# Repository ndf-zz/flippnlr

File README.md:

# Flippnlr - 4x5 DiY Flipdot Panel

How _not_ to make a DiY electromechanical "Flip-Dot" matrix display.

## Coil Winding

M3 steel screw and heat shrink tube.

Shrink onto screw.

Add slight glue fillet.

Mount in winder.

Wind about 1000 turns.

Finish with a thin layer of glue.

## Flipdot Mechanism

FreeCAD model: [flipdot.FCStd](flipdot.FCStd)

SLS printed housing.

File contact areas.

Smooth contact areas with fine sandpaper.

Tap mounting and coil holes with M3 thread.

## Pixel Preparation

## Panel Assembly

Kicad PCB: [flippnlr.pro](flippnlr.pro)

## Interface

 - D Data input (SDI)
 - DC Data clock (SCK)
 - RC Latch Clock 

## License

CC0 Public Domain

To the extent possible under law, the author(s) have dedicated
all copyright and related and neighboring rights to this software
to the public domain worldwide. This software is distributed
without any warranty.

You should have received a copy of the CC0 Public Domain Dedication
along with this software. If not, see:

http://creativecommons.org/publicdomain/zero/1.0/

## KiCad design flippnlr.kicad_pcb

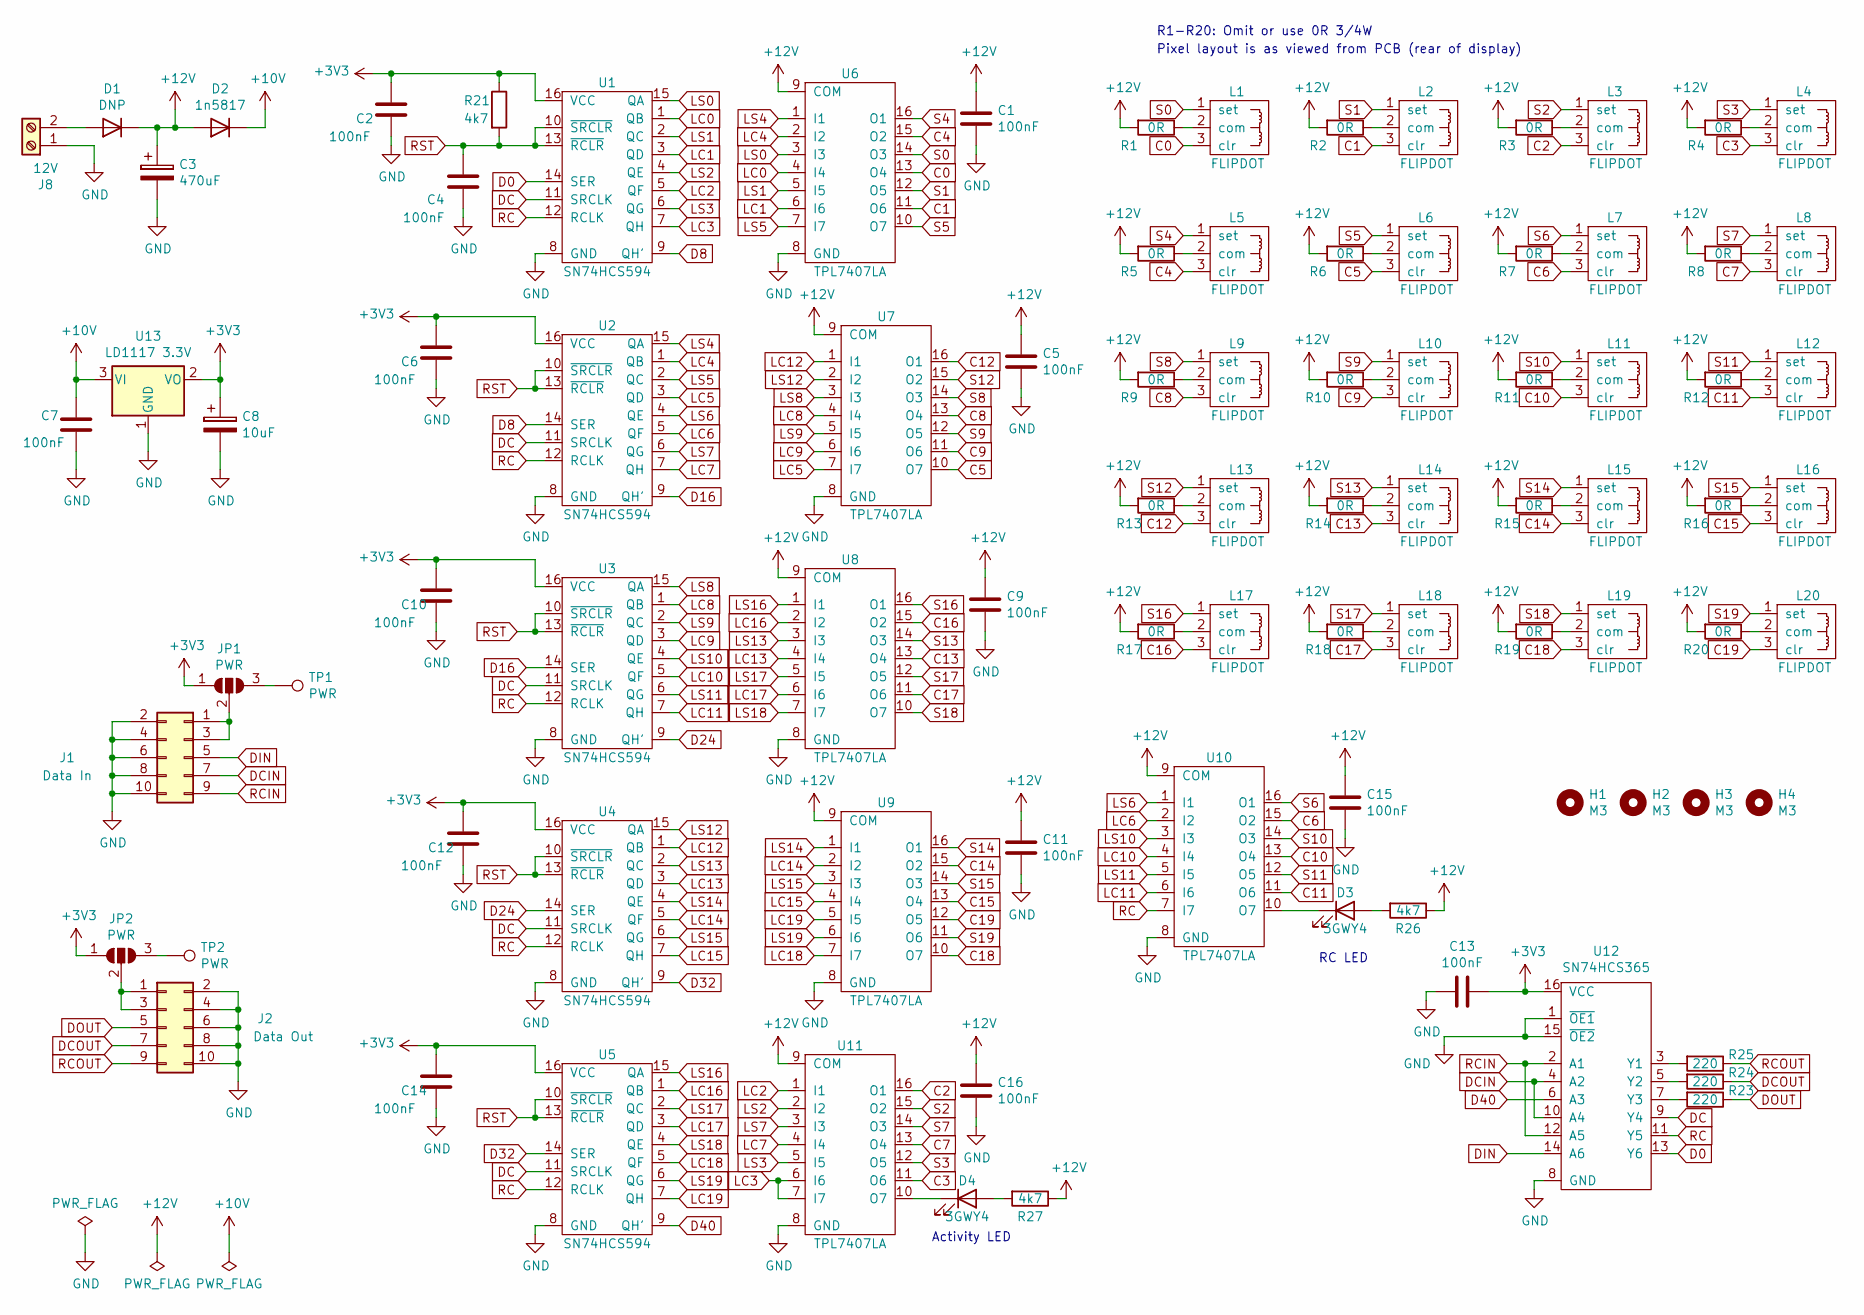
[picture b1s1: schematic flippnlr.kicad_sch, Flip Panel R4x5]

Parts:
C1, C2, C4, C5, C6, C7, C9, C10, C11, C12, C13, C14, C15, C16: 100nF; C_0805_2012Metric_Pad1.15x1.40mm_HandSolder
C3: 470uF; CP_Radial_D10.0mm_P5.00mm
C8: 10uF; CP_Radial_D5.0mm_P2.50mm
D1: DNP; D_A-405_P10.16mm_Horizontal
D2: 1n5817; D_A-405_P10.16mm_Horizontal
D3, D4: 3GWY4; LED_D3.0mm
H1, H2, H3, H4: M3; MountingHole_3.2mm_M3
J1: Data In; IDC-Header_2x05_P2.54mm_Vertical
J2: Data Out; IDC-Header_2x05_P2.54mm_Vertical
J8: 12V; TerminalBlock_Phoenix_PT-1,5-2-5.0-H_1x02_P5.00mm_Horizontal
JP1, JP2: PWR; SolderJumper-3_P1.3mm_Open_RoundedPad1.0x1.5mm
L1, L2, L3, L4, L5, L6, L7, L8, L9, L10, L11, L12, L13, L14, L15, L16, L17, L18, L19, L20: FLIPDOT; Flipdot
R1, R2, R3, R4, R5, R6, R7, R8, R9, R10, R11, R12, R13, R14, R15, R16, R17, R18, R19, R20: 0R; R_2010_5025Metric_Pad1.52x2.65mm_HandSolder
R21, R26, R27: 4k7; R_0805_2012Metric_Pad1.15x1.40mm_HandSolder
R23, R24, R25: 220; R_0805_2012Metric_Pad1.15x1.40mm_HandSolder
TP1, TP2: PWR; TestPoint_Pad_D2.0mm
U1, U2, U3, U4, U5: SN74HCS594; SOP-16_4.4x10.4mm_P1.27mm
U6, U7, U8, U9, U10, U11: TPL7407LA; SOP-16_4.4x10.4mm_P1.27mm
U12: SN74HCS365; SOP-16_4.4x10.4mm_P1.27mm
U13: LD1117 3.3V; SOT-223-3_TabPin2

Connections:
+3V3: C2.1, C6.1, C8.1, C10.1, C12.1, C13.1, C14.1, JP1.1 (A), JP2.1 (A), R21.1, U1.16 (VCC), U2.16 (VCC), U3.16 (VCC), U4.16 (VCC), U5.16 (VCC), U12.16 (VCC), U13.2 (VO)
+10V: C7.1, D2.1 (K), U13.3 (VI)
+12V: C1.1, C3.1, C5.1, C9.1, C11.1, C15.1, C16.1, D1.1 (K), D2.2 (A), R1.2, R2.2, R3.2, R4.2, R5.2, R6.2, R7.2, R8.2, R9.2, R10.2, R11.2, R12.2, R13.2, R14.2, R15.2, R16.2, R17.2, R18.2, R19.2, R20.2, R26.1, R27.1, U6.9 (COM), U7.9 (COM), U8.9 (COM), U9.9 (COM), U10.9 (COM), U11.9 (COM)
C0: L1.3 (clr), U6.13 (O4)
C1: L2.3 (clr), U6.11 (O6)
C2: L3.3 (clr), U11.16 (O1)
C3: L4.3 (clr), U11.11 (O6)
C4: L5.3 (clr), U6.15 (O2)
C5: L6.3 (clr), U7.10 (O7)
C6: L7.3 (clr), U10.15 (O2)
C7: L8.3 (clr), U11.13 (O4)
C8: L9.3 (clr), U7.13 (O4)
C9: L10.3 (clr), U7.11 (O6)
C10: L11.3 (clr), U10.13 (O4)
C11: L12.3 (clr), U10.11 (O6)
C12: L13.3 (clr), U7.16 (O1)
C13: L14.3 (clr), U8.13 (O4)
C14: L15.3 (clr), U9.15 (O2)
C15: L16.3 (clr), U9.13 (O4)
C16: L17.3 (clr), U8.15 (O2)
C17: L18.3 (clr), U8.11 (O6)
C18: L19.3 (clr), U9.10 (O7)
C19: L20.3 (clr), U9.12 (O5)
D0: U1.14 (SER), U12.13 (Y6)
D8: U1.9 (QH'), U2.14 (SER)
D16: U2.9 (QH'), U3.14 (SER)
D24: U3.9 (QH'), U4.14 (SER)
D32: U4.9 (QH'), U5.14 (SER)
D40: U5.9 (QH'), U12.6 (A3)
DC: U1.11 (SRCLK), U2.11 (SRCLK), U3.11 (SRCLK), U4.11 (SRCLK), U5.11 (SRCLK), U12.9 (Y4)
DCIN: J1.7, U12.4 (A2), U12.10 (A4)
DCOUT: J2.7, R24.1
DIN: J1.5, U12.14 (A6)
DOUT: J2.5, R23.1
GND: C1.2, C2.2, C3.2, C4.1, C5.2, C6.2, C7.2, C8.2, C9.2, C10.2, C11.2, C12.2, C13.2, C14.2, C15.2, C16.2, J1.2, J1.4, J1.6, J1.8, J1.10, J2.2, J2.4, J2.6, J2.8, J2.10, J8.1, U1.8 (GND), U2.8 (GND), U3.8 (GND), U4.8 (GND), U5.8 (GND), U6.8 (GND), U7.8 (GND), U8.8 (GND), U9.8 (GND), U10.8 (GND), U11.8 (GND), U12.1 (~OE1), U12.8 (GND), U12.15 (~OE2), U13.1 (GND)
LC0: U1.1 (QB), U6.4 (I4)
LC1: U1.3 (QD), U6.6 (I6)
LC2: U1.5 (QF), U11.1 (I1)
LC3: U1.7 (QH), U11.6 (I6), U11.7 (I7)
LC4: U2.1 (QB), U6.2 (I2)
LC5: U2.3 (QD), U7.7 (I7)
LC6: U2.5 (QF), U10.2 (I2)
LC7: U2.7 (QH), U11.4 (I4)
LC8: U3.1 (QB), U7.4 (I4)
LC9: U3.3 (QD), U7.6 (I6)
LC10: U3.5 (QF), U10.4 (I4)
LC11: U3.7 (QH), U10.6 (I6)
LC12: U4.1 (QB), U7.1 (I1)
LC13: U4.3 (QD), U8.4 (I4)
LC14: U4.5 (QF), U9.2 (I2)
LC15: U4.7 (QH), U9.4 (I4)
LC16: U5.1 (QB), U8.2 (I2)
LC17: U5.3 (QD), U8.6 (I6)
LC18: U5.5 (QF), U9.7 (I7)
LC19: U5.7 (QH), U9.5 (I5)
LS0: U1.15 (QA), U6.3 (I3)
LS1: U1.2 (QC), U6.5 (I5)
LS2: U1.4 (QE), U11.2 (I2)
LS3: U1.6 (QG), U11.5 (I5)
LS4: U2.15 (QA), U6.1 (I1)
LS5: U2.2 (QC), U6.7 (I7)
LS6: U2.4 (QE), U10.1 (I1)
LS7: U2.6 (QG), U11.3 (I3)
LS8: U3.15 (QA), U7.3 (I3)
LS9: U3.2 (QC), U7.5 (I5)
LS10: U3.4 (QE), U10.3 (I3)
LS11: U3.6 (QG), U10.5 (I5)
LS12: U4.15 (QA), U7.2 (I2)
LS13: U4.2 (QC), U8.3 (I3)
LS14: U4.4 (QE), U9.1 (I1)
LS15: U4.6 (QG), U9.3 (I3)
LS16: U5.15 (QA), U8.1 (I1)
LS17: U5.2 (QC), U8.5 (I5)
LS18: U5.4 (QE), U8.7 (I7)
LS19: U5.6 (QG), U9.6 (I6)
unnamed: D1.2 (A), J8.2
unnamed: D3.1 (K), U10.10 (O7)
unnamed: D3.2 (A), R26.2
unnamed: D4.1 (K), U11.10 (O7)
unnamed: D4.2 (A), R27.2
unnamed: J1.1, J1.3, JP1.2 (C)
unnamed: J2.1, J2.3, JP2.2 (C)
unnamed: JP1.3 (B), TP1.1
unnamed: JP2.3 (B), TP2.1
unnamed: L1.2 (com), R1.1
unnamed: L2.2 (com), R2.1
unnamed: L3.2 (com), R3.1
unnamed: L4.2 (com), R4.1
unnamed: L5.2 (com), R5.1
unnamed: L6.2 (com), R6.1
unnamed: L7.2 (com), R7.1
unnamed: L8.2 (com), R8.1
unnamed: L9.2 (com), R9.1
unnamed: L10.2 (com), R10.1
unnamed: L11.2 (com), R11.1
unnamed: L12.2 (com), R12.1
unnamed: L13.2 (com), R13.1
unnamed: L14.2 (com), R14.1
unnamed: L15.2 (com), R15.1
unnamed: L16.2 (com), R16.1
unnamed: L17.2 (com), R17.1
unnamed: L18.2 (com), R18.1
unnamed: L19.2 (com), R19.1
unnamed: L20.2 (com), R20.1
unnamed: R23.2, U12.7 (Y3)
unnamed: R24.2, U12.5 (Y2)
unnamed: R25.2, U12.3 (Y1)
RC: U1.12 (RCLK), U2.12 (RCLK), U3.12 (RCLK), U4.12 (RCLK), U5.12 (RCLK), U10.7 (I7), U12.11 (Y5)
RCIN: J1.9, U12.2 (A1), U12.12 (A5)
RCOUT: J2.9, R25.1
RST: C4.2, R21.2, U1.10 (~SRCLR), U1.13 (~RCLR), U2.10 (~SRCLR), U2.13 (~RCLR), U3.10 (~SRCLR), U3.13 (~RCLR), U4.10 (~SRCLR), U4.13 (~RCLR), U5.10 (~SRCLR), U5.13 (~RCLR)
S0: L1.1 (set), U6.14 (O3)
S1: L2.1 (set), U6.12 (O5)
S2: L3.1 (set), U11.15 (O2)
S3: L4.1 (set), U11.12 (O5)
S4: L5.1 (set), U6.16 (O1)
S5: L6.1 (set), U6.10 (O7)
S6: L7.1 (set), U10.16 (O1)
S7: L8.1 (set), U11.14 (O3)
S8: L9.1 (set), U7.14 (O3)
S9: L10.1 (set), U7.12 (O5)
S10: L11.1 (set), U10.14 (O3)
S11: L12.1 (set), U10.12 (O5)
S12: L13.1 (set), U7.15 (O2)
S13: L14.1 (set), U8.14 (O3)
S14: L15.1 (set), U9.16 (O1)
S15: L16.1 (set), U9.14 (O3)
S16: L17.1 (set), U8.16 (O1)
S17: L18.1 (set), U8.12 (O5)
S18: L19.1 (set), U8.10 (O7)
S19: L20.1 (set), U9.11 (O6)

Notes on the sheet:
R1-R20: Omit or use 0R 3/4W
RC LED
Pixel layout is as viewed from PCB (rear of display)
Activity LED

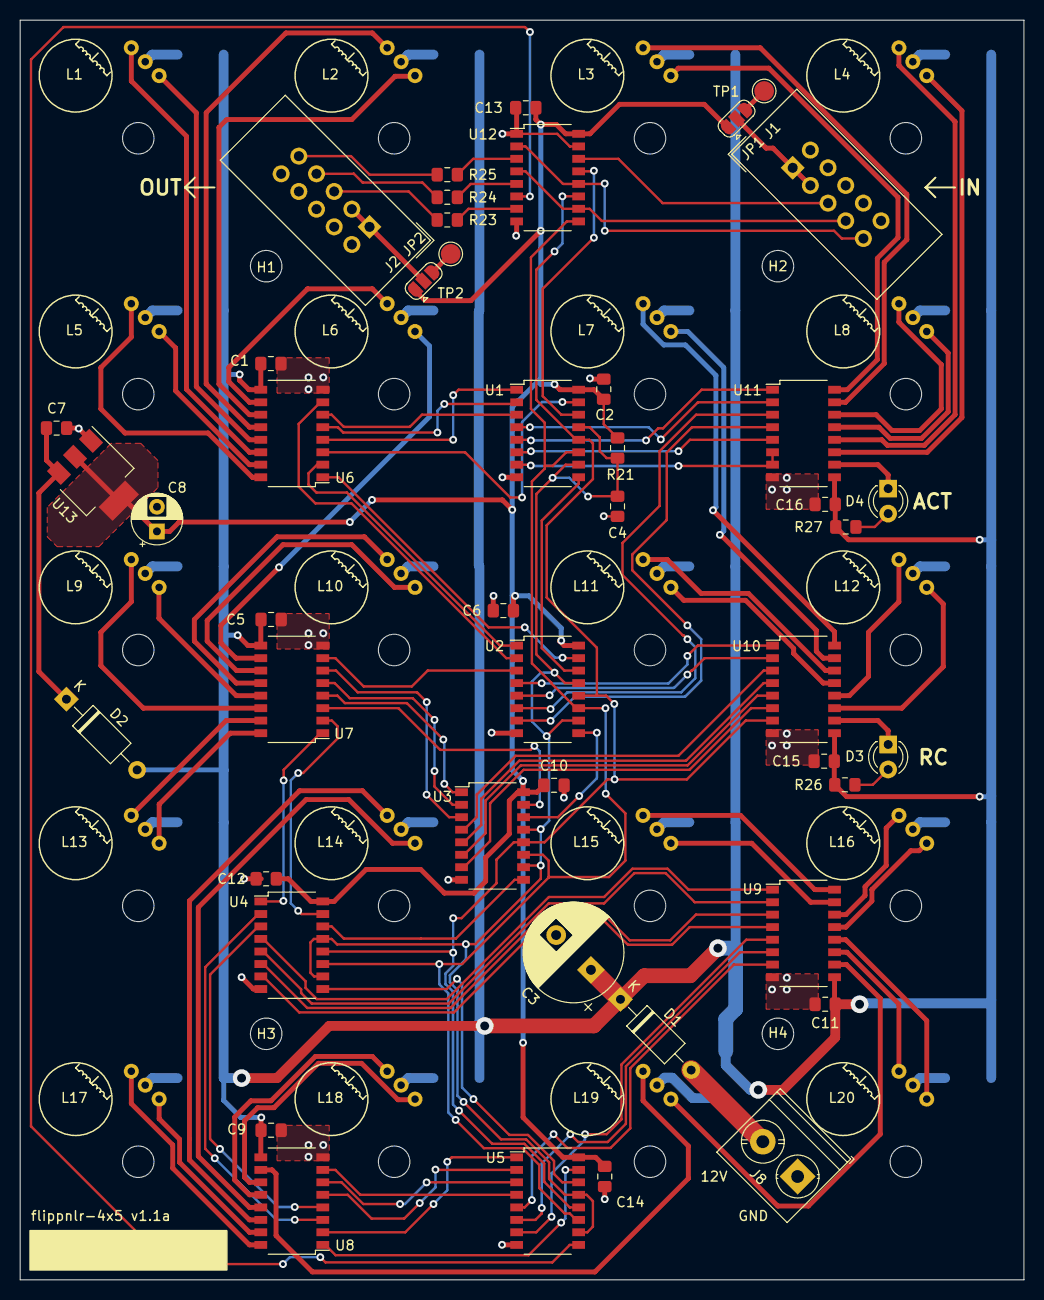
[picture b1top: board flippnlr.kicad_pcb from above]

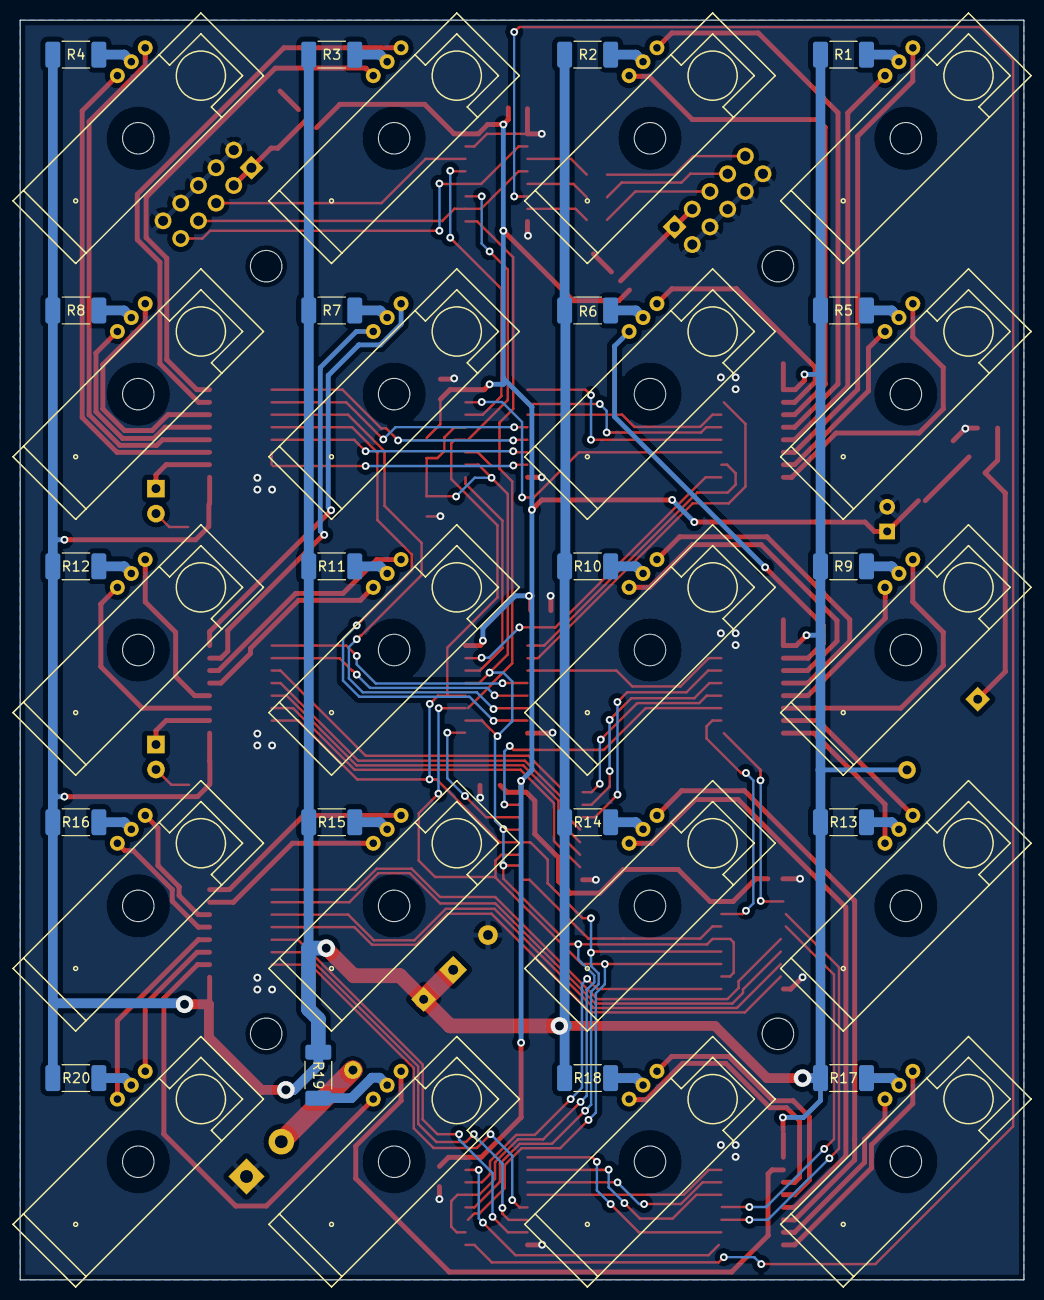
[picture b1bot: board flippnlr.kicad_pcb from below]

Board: 2 copper layers, 102.0 x 128.0 mm, 90 parts (20 on the bottom side), 131 nets.

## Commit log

2021-09-06 add pixel cad model
2021-09-06 add kicad project
2021-09-11 fix kicad lib path and begin layout
2021-09-12 move images to subdir
2021-09-12 reroute signals slightly
2021-09-12 pcb roughly routed
2021-09-14 correct mis-wired U5
2021-09-14 correct Lx3/Lx7
2021-09-15 prepare for gerbers
2021-09-15 first prototype
2021-10-03 add coil winding instruction
2021-10-03 readme typos
2021-10-08 update winding procedure
2021-10-09 alter start wire to avoid shorts
2021-10-20 add panel image and spi timing
2022-04-13 update photos and readme
2024-03-09 Update to Kicad v6
2024-03-09 Rename repository to match Kicad project
